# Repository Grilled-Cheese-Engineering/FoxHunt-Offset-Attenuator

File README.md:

# FoxHunt Offset Attenuator
A simple foxhunt offset attenuator! Original circuit design by John KC9ON. More information coming soon!

This project was made 100% WITHOUT AI. We do not use AI for Grilled Cheese Engineering Projects.

## How it Works

This style of attenuator is very simple to operate but very powerful. It is operated with just a single potentiometer to adjust the attenuation power. A 4.00MHz clock is "injected" into the RF signal which creates an effect called intermodulation which creates attenuated versions of the frequency 4.00MHz up and down. Below is a picture from a test using the V1 Attenuator. 

The large peak is the frequency that something is transmitting and peak to the left and right is 4.00MHz from the transmit frequency. On the most sensitive mode, there is 25dBm attenuation already!

While fox hunting, tune either 4.00MHz up or down to listen to the attenuated signal.

## Attenuator Versions

### V2 Attenuator

This is the V2 attenuator. This revised and updated version of the attenuator incorporates a few key improvement and modifications. It is a cross between the V7 and V5 attenuator by John KC9ON. One of the biggest changes is a shift from SMD to Through Hole parts so it can be easily assembled and sold as a kit. It also only has a single potentiometer which makes the attenuator easier to operate.

The V2 is also a tad cheaper than the V1 and the board is larger in size so a 9v battery fits behind it perfectly.

I will be also making an alternate layout of this PCB to fit in a Lowes PVC Conduit so it can be integrated directly into a yagi antenna. More info on that soon...

---

### V1 Attenuator

This is the V1 attenuator. This version was made with primarly SMD parts and based on John KC9ON's V5 Offset Attenuator. This version is not available any more because I made a better version and there is no reason to use this one anymore.

## Credit

This attenuator was adapted from John KC9ON's Offset Fox hunt attenuator. Check out his website here [KC9ON.com](https://kc9on.com). 

## Commercial Use

Grilled Cheese Engineering plans to sell this attenuator design online soon and has acquired permission from the original designer of the circuit (John KC9ON) to sell this attenuator online.

## Notes

If you try pulling this project yourself, some component symbols might be missing and you will have to download and install them yourself. This is because I was silly and didn't put all of the part libraries in this project.

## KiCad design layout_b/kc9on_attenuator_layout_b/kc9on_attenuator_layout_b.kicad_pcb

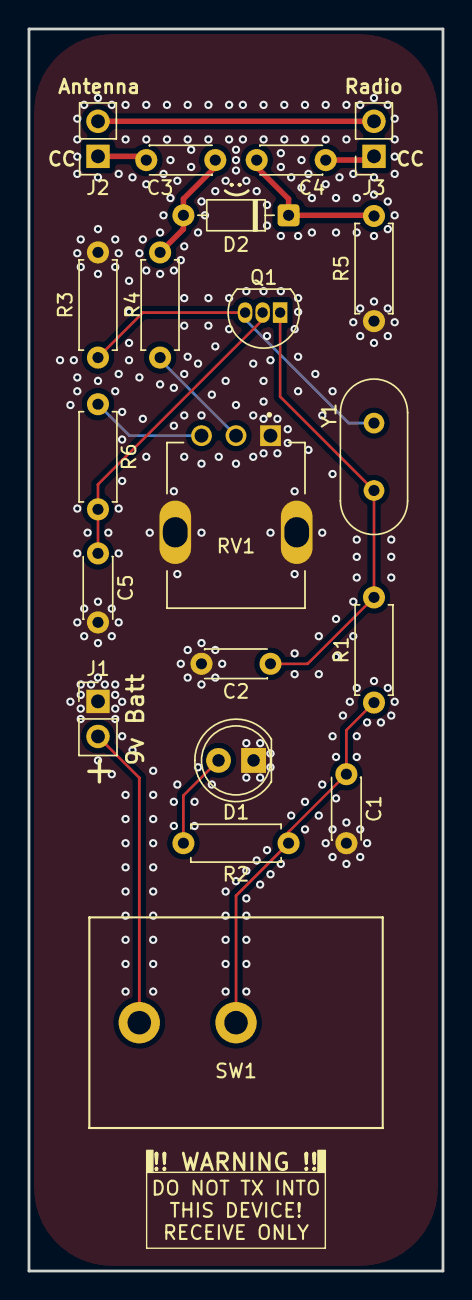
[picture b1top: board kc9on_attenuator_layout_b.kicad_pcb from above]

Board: 2 copper layers, 30.0 x 90.0 mm, 20 parts (0 on the bottom side), 14 nets.

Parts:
C1: 0.1uF; C_Disc_D4.3mm_W1.9mm_P5.00mm
C2, C5: 15pF; C_Disc_D4.3mm_W1.9mm_P5.00mm
C3, C4: 220pF; C_Disc_D4.3mm_W1.9mm_P5.00mm
D1: 5mm; LED_D5.0mm
D2: 1N4148; D_DO-35_SOD27_P7.62mm_Horizontal
J1: 9v Battery; PinHeader_1x02_P2.54mm_Vertical
J2: Antenna; PinSocket_1x02_P2.54mm_Vertical
J3: Radio; PinSocket_1x02_P2.54mm_Vertical
Q1: J113; TO-92L_Inline
R1: 1K; R_Axial_DIN0207_L6.3mm_D2.5mm_P7.62mm_Horizontal
R2, R5: 2.2K; R_Axial_DIN0207_L6.3mm_D2.5mm_P7.62mm_Horizontal
R3: 1M; R_Axial_DIN0207_L6.3mm_D2.5mm_P7.62mm_Horizontal
R4: 4.7K; R_Axial_DIN0207_L6.3mm_D2.5mm_P7.62mm_Horizontal
R6: 2.2k; R_Axial_DIN0207_L6.3mm_D2.5mm_P7.62mm_Horizontal
RV1: 10K; TRIM_PT01-D225D-B103
SW1: RA131C1121; SW_RA131C1121_EWI
Y1: 4.000MHz; Crystal_HC49-4H_Vertical

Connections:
GND: C1.2, C2.2, C5.2, D1.1 (K), J1.1, R3.2, R5.1, RV1.1, RV1.MP (MountPin)
unnamed: C1.1, R1.1, R2.1, SW1.2
unnamed: D1.2 (A), R2.2
unnamed: C3.1, D2.2 (A), R4.2
unnamed: C4.1, D2.1 (K), R5.2
unnamed: J1.2, SW1.1
unnamed: J2.2 (Ext), J3.2 (Ext)
unnamed: C3.2, J2.1 (In)
unnamed: C4.2, J3.1 (In)
unnamed: C2.1, Q1.1 (D), R1.2, Y1.2
unnamed: Q1.3 (G), R3.1, Y1.1
unnamed: C5.1, Q1.2 (S), R6.2
unnamed: R4.1, RV1.2
unnamed: R6.1, RV1.3
